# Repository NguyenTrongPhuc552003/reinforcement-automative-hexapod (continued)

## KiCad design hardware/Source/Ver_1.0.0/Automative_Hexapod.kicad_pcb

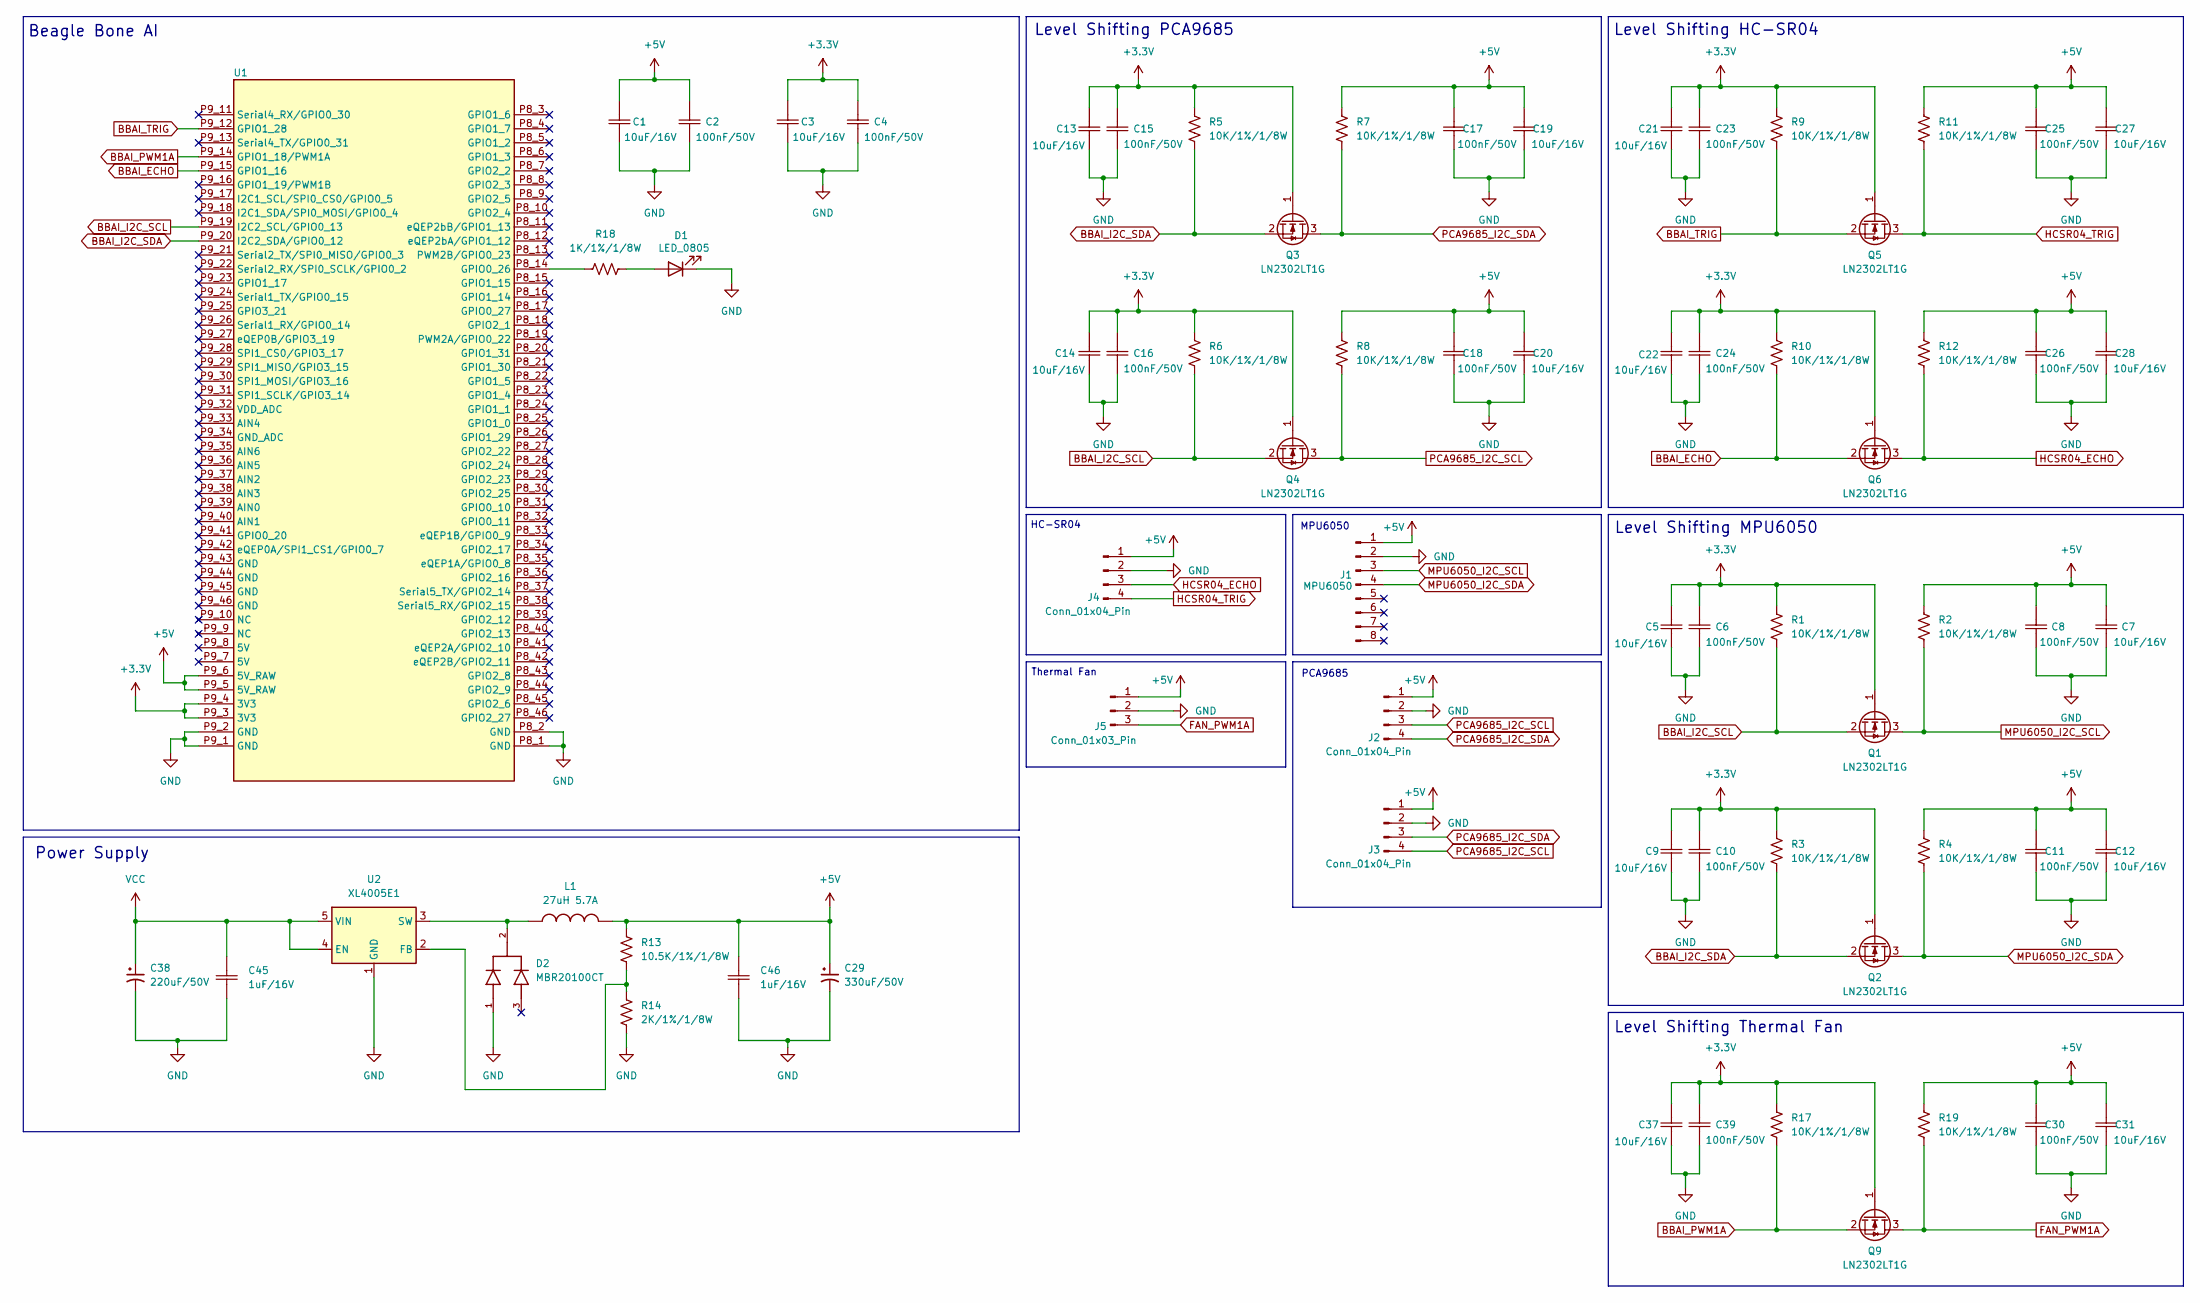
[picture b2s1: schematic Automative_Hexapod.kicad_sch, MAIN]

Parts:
C1, C3, C5, C7, C9, C12, C13, C14, C19, C20, C21, C22, C27, C28, C31, C37: 10uF/16V; Ceramic_Cap_0805
C2, C4, C6, C8, C10, C11, C15, C16, C17, C18, C23, C24, C25, C26, C30, C39: 100nF/50V; Ceramic_Cap_0805
C29: 330uF/50V; CP_Elec_10x10.5
C38: 220uF/50V; CP_Elec_10x10.5
C45, C46: 1uF/16V; Ceramic_Cap_0805
D1: LED_0805
D2: MBR20100CT; TO-220-3
J1: MPU6050
J2, J3, J4: Conn_01x04_Pin; PinHeader_1x04_P1.00mm_Vertical
J5: Conn_01x03_Pin; PinHeader_1x03_P1.00mm_Vertical
L1: 27uH 5.7A; IND_CDRH127_LDNP-470MC_SUM
Q1, Q2, Q3, Q4, Q5, Q6, Q9: LN2302LT1G; SOT23
R1, R2, R3, R4, R5, R6, R7, R8, R9, R10, R11, R12, R17, R19: 10K/1%/1/8W; Res_0805
R13: 10.5K/1%/1/8W; Res_0805
R14: 2K/1%/1/8W; Res_0805
R18: 1K/1%/1/8W; Res_0805
U1: BeagleBone_AI
U2: XL4005E1; TO-263-5

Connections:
+3.3V: C3.2, C4.2, C5.2, C6.2, C9.2, C10.2, C13.2, C14.2, C15.2, C16.2, C21.2, C22.2, C23.2, C24.2, C37.2, C39.2, Q1.1 (G), Q2.1 (G), Q3.1 (G), Q4.1 (G), Q5.1 (G), Q6.1 (G), Q9.1 (G), R1.2, R3.2, R5.2, R6.2, R9.2, R10.2, R17.2, U1.P9_3 (3V3), U1.P9_4 (3V3)
+5V: C1.2, C2.2, C7.2, C8.2, C11.2, C12.2, C17.2, C18.2, C19.2, C20.2, C25.2, C26.2, C27.2, C28.2, C29.1, C30.2, C31.2, C46.2, J1.1, J2.1, J3.1, J4.1, J5.1, L1.2, R2.2, R4.2, R7.2, R8.2, R11.2, R12.2, R13.2, R19.2, U1.P9_5 (5V_RAW), U1.P9_6 (5V_RAW)
BBAI_ECHO: Q6.2 (S), R10.1, U1.P9_15 (GPIO1_16)
BBAI_I2C_SCL: Q1.2 (S), Q4.2 (S), R1.1, R6.1, U1.P9_19 (I2C2_SCL/GPIO0_13)
BBAI_I2C_SDA: Q2.2 (S), Q3.2 (S), R3.1, R5.1, U1.P9_20 (I2C2_SDA/GPIO0_12)
BBAI_PWM1A: Q9.2 (S), R17.1, U1.P9_14 (GPIO1_18/PWM1A)
BBAI_TRIG: Q5.2 (S), R9.1, U1.P9_12 (GPIO1_28)
FAN_PWM1A: J5.3, Q9.3 (D), R19.1
GND: C1.1, C2.1, C3.1, C4.1, C5.1, C6.1, C7.1, C8.1, C9.1, C10.1, C11.1, C12.1, C13.1, C14.1, C15.1, C16.1, C17.1, C18.1, C19.1, C20.1, C21.1, C22.1, C23.1, C24.1, C25.1, C26.1, C27.1, C28.1, C29.2, C30.1, C31.1, C37.1, C38.2, C39.1, C45.1, C46.1, D1.1 (K), D2.1, J1.2, J2.2, J3.2, J4.2, J5.2, R14.1, U1.P8_1 (GND), U1.P8_2 (GND), U1.P9_1 (GND), U1.P9_2 (GND), U2.1 (GND)
HCSR04_ECHO: J4.3, Q6.3 (D), R12.1
HCSR04_TRIG: J4.4, Q5.3 (D), R11.1
MPU6050_I2C_SCL: J1.3, Q1.3 (D), R2.1
MPU6050_I2C_SDA: J1.4, Q2.3 (D), R4.1
unnamed: D1.2 (A), R18.2
unnamed: R18.1, U1.P8_14 (GPIO0_26)
unnamed: R13.1, R14.2, U2.2 (FB)
unnamed: D2.2, L1.1, U2.3 (SW)
PCA9685_I2C_SCL: J2.3, J3.4, Q4.3 (D), R8.1
PCA9685_I2C_SDA: J2.4, J3.3, Q3.3 (D), R7.1
VCC: C38.1, C45.2, U2.4 (EN), U2.5 (VIN)

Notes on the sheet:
PCA9685
HC-SR04
Thermal Fan
Level Shifting MPU6050
Beagle Bone AI
Level Shifting HC-SR04
Level Shifting Thermal Fan
MPU6050
Level Shifting PCA9685
Power Supply

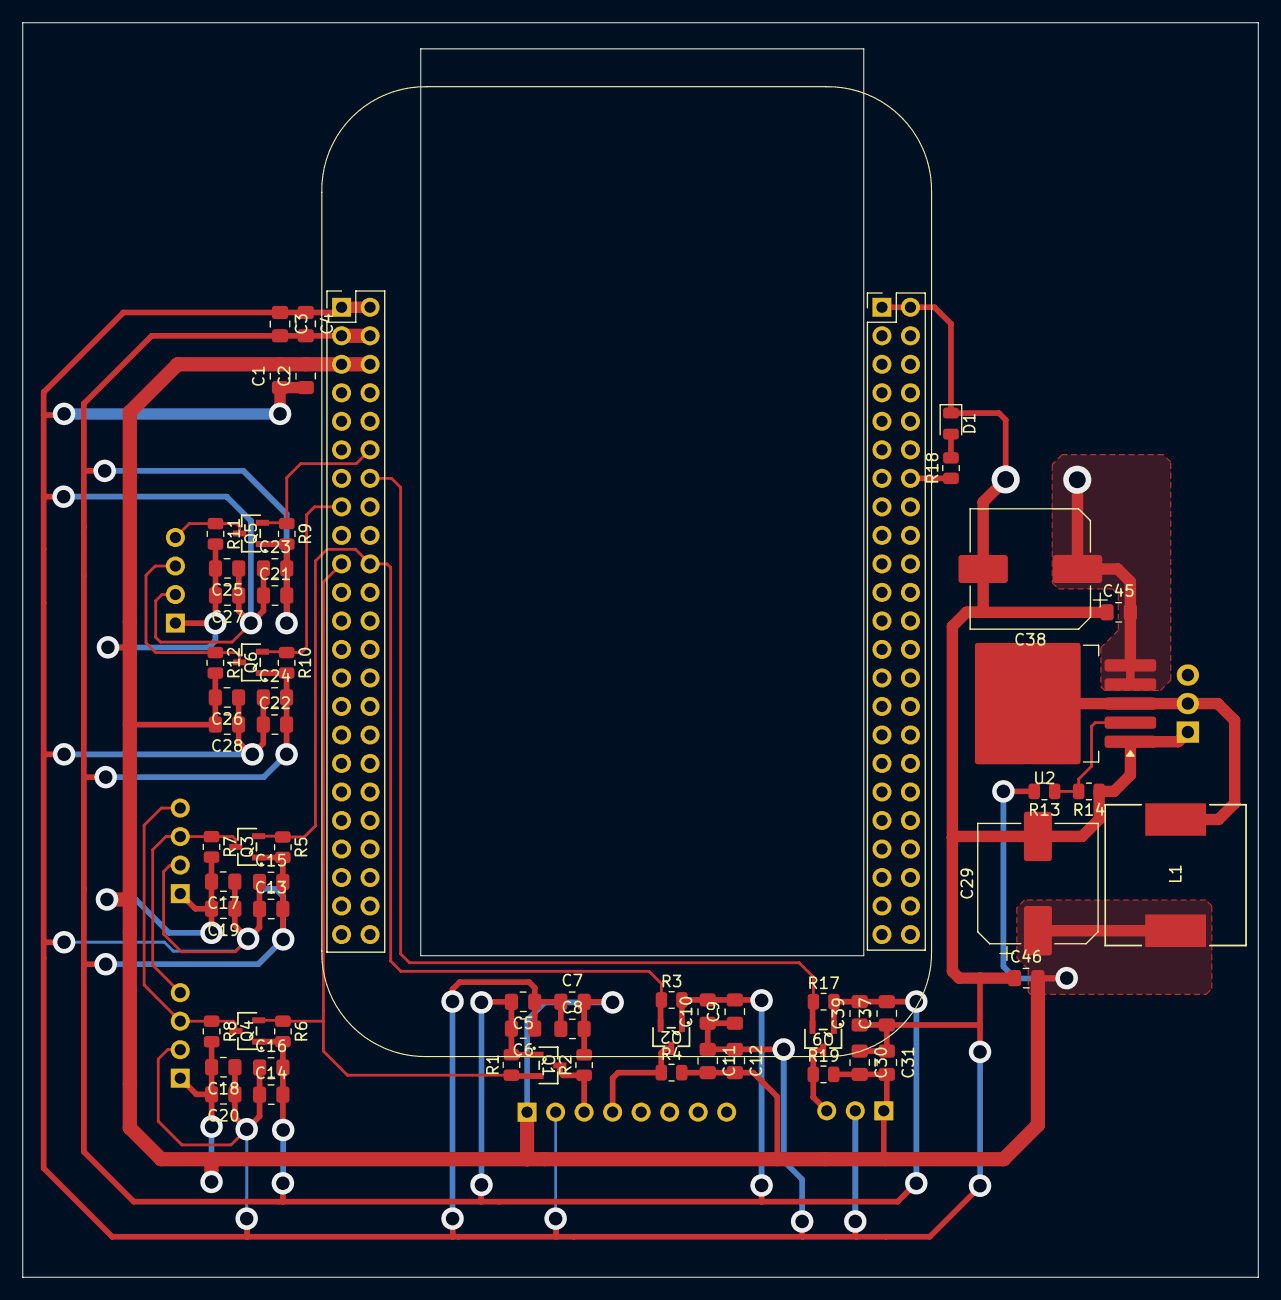
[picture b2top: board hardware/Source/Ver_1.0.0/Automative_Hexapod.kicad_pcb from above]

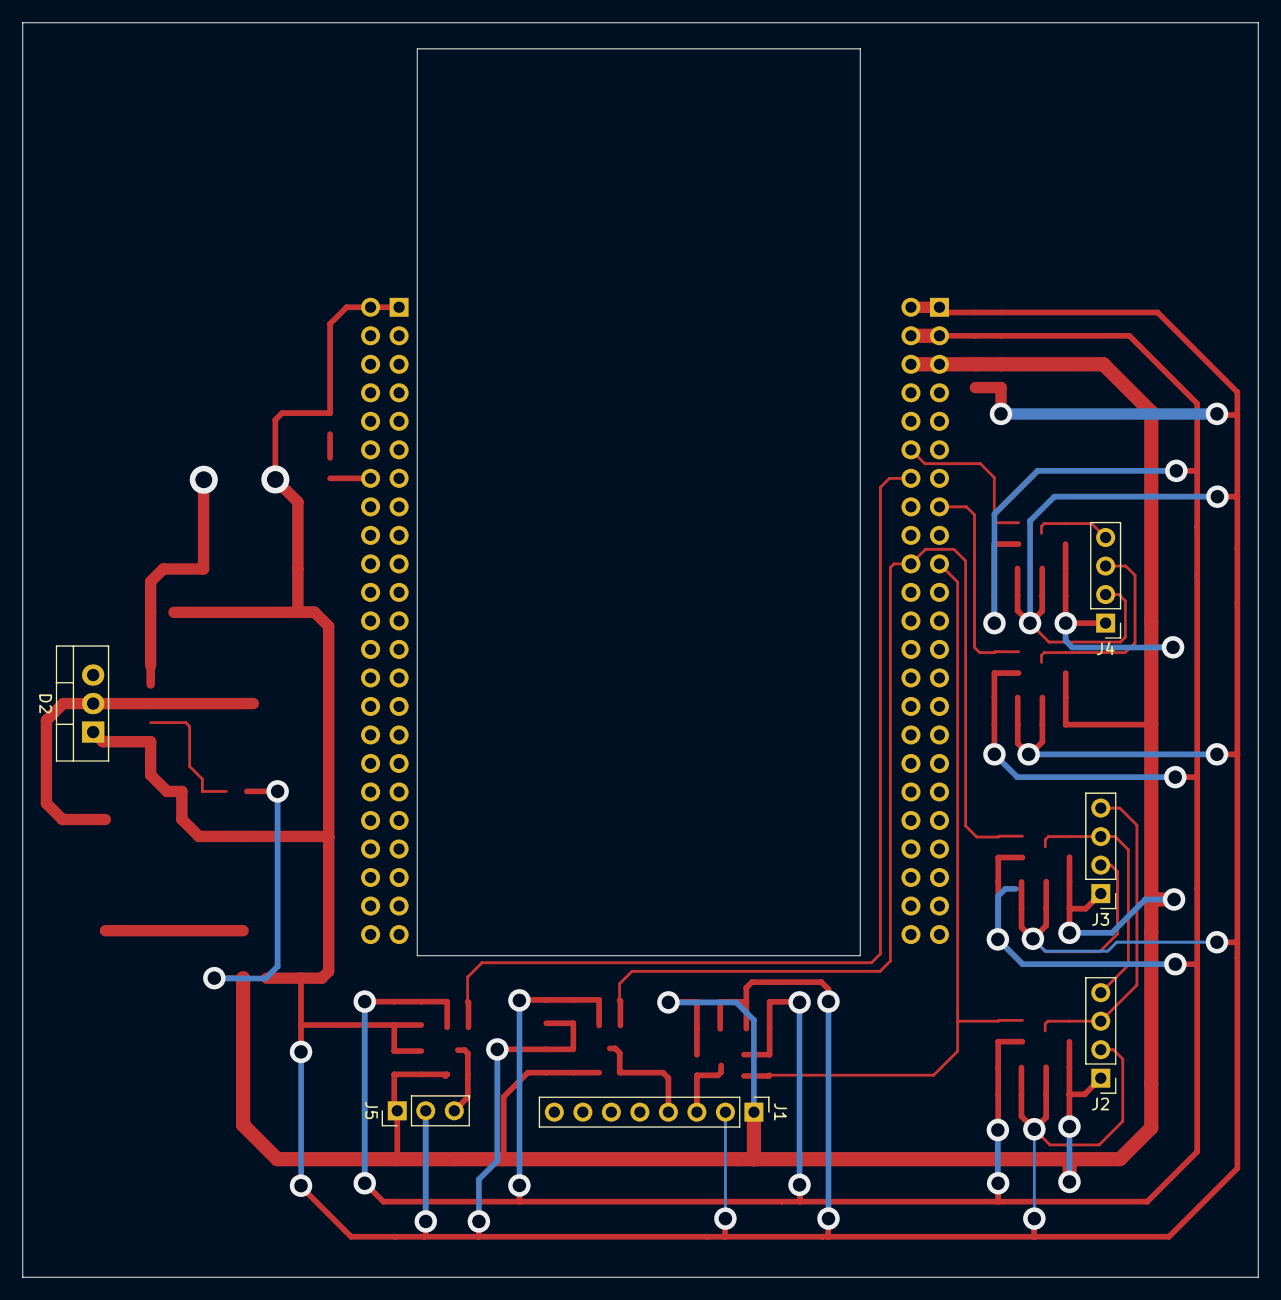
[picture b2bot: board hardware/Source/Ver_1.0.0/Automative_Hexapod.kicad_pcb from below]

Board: 2 copper layers, 110.1 x 111.8 mm, 70 parts (6 on the bottom side), 20 nets.

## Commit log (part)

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2025-02-18 Add some new features
2025-02-18 Extend and Develop some new features
2025-02-19 Add clean option for make command
2025-02-19 Modify our kernel driver for optimizations
2025-02-19 Modify our user space programs for optimizations
2025-02-20 Modify and update new features
2025-02-20 Update .gitignore and hexapod kernel driver
2025-02-22 websocket
2025-02-22 Rewrite and update user space sources
2025-02-23 Creating more static/dynamic libraries for communication between layers
2025-02-25 Intergrating the common libraries between the layers to enhance the performance
2025-02-25 Update the latest to documents
2025-02-26 Update the inverse kinematics algorithm
2025-02-26 Optimizing the general hexapod structure
2025-02-28 Update the user space patches
2025-03-05 Big updates
2025-03-06 Create an extra hexapod controller for keyboard
2025-03-10 Rewriting the user space applications from C to Cpp
2025-03-11 Upgrade the basic hexapod application features
2025-03-11 Modify the main README.md
2025-03-11 Finish the build system environment with Dockerfile
2025-03-11 Move the websocket program to the new hierachy structure
2025-03-20 Patch the kernel drivers related to the second PCA9685
2025-03-21 Modify and repair the some kernel drivers
2025-03-21 Re-structure the user space programs
2025-03-21 Rename the docker-entrypoint.sh
2025-03-24 Optimize the kernel drivers and user space programs by making them better
2025-03-27 Re-structing the user space programs's structures by making theirs more expandable and maintainable easily
2025-03-28 Patching the MPU6050 wake-up error after re-running the testing program for this peripheral
2025-03-28 Refactoring the deleted old files to new names
2025-03-29 Replace C with Cpp syntax
2025-04-03 Create an extra utils directory to make the project's structure looks better
2025-04-03 Move both install.sh and monitor.sh bash scripts to the utils directory
2025-04-03 Add both OpenCL and TIDL APIs submodule to the hexapod
2025-04-04 Add Twin Delayed DDPG algorithm implementations to improve the hexapod's movement
2025-04-11 Rename the peripherals's document names
2025-04-11 Hexapod Monitoring Application by Qt Framework
2025-04-11 Modify a little bit
2025-04-11 Modify and update the Docker environment
2025-04-11 Upgrade the build.sh script' features based on td3learn
2025-04-11 Add the build directory that contains Makefile configuration for this Qt application
2025-04-12 Update and enhance the Qt hexapod UI
2025-04-12 Fix the syntax error by replacing device to artifact
2025-04-12 Enhance the td3 algorithms based on its related API functions
2025-04-12 Remove the unnescessary libraries
2025-04-12 Rename the Qt hexapod project
2025-04-14 Ignoring the out directory
2025-04-14 Creating a building script for UML diagrams from docs/diagrams directory
2025-04-14 Adding the extra UML diagrams building with export.sh script support
2025-04-14 Adding an extra UML diagrams directory to create a system overview better
2025-04-14 Change the generated output's title without space
2025-04-14 Update the building background
2025-04-14 Update the latest documents
2025-04-15 Rename the Qt hexapod application
2025-04-15 Remove the old files
2025-04-15 Add the build configuration
2025-04-21 Modifying and fixing the td3learn algorithm
2025-04-21 Update hexapod application
2025-04-21 Update quickstart document
2025-04-21 Modify TD3Learn CMake configuration for enhancement
2025-04-26 Add SIM7600CE module
2025-04-26 Create MPU6050 and PCA9685 device tree for the better cases
2025-05-03 Fix the cleanup duplication
2025-05-03 Rename the related uml diagrams for TD3 algorithm
2025-05-03 Rename TD3 algoritm
2025-05-20 Add some comment
2025-05-20 Remove setup.sh bash script
2025-05-20 Modify and update td3learn
2025-05-20 Update Docker environment
2025-05-20 Update entrypoint.sh script to match with the current Dockerfile environment
2025-05-20 Update more features to docker-compose.yml file
2025-05-20 Change the path from static to dynamic
2025-05-20 Modify and update this script to add the QtUI building and cleaning operations
2025-05-20 Using new docker hierachy instead of the old common
2025-05-20 remove the generated file
2025-05-27 Turn this qtui into a submodule
2025-05-27 Update the diagram outputs
2025-05-27 Modify the ignored python
2025-05-27 Add a testing bash script
2025-05-27 Start to integrate the gitlab CICD process into our project
2025-05-27 Update the building script
2025-06-07 Isolate the Qt hexapod app from this repo
2025-06-07 Remove tracked PNG files from docs/diagrams/out/
2025-06-07 Ignore the generated .png files from diagram directory
2025-06-07 Keep diagram PNG files tracked in Git
2025-06-07 Create a directory to stored the generated files after building the UML programs
2025-06-07 Add the HC-SR04 sensor's documents
2025-06-08 Change the app features
2025-06-14 Modify and add more changes to support a new integrated sensor
2025-06-15 Add the BeagleBone AI schematic
2025-06-15 Update the ultrasonic API functions's implementations using sysfs interface instead of libgpiod usage
2025-06-15 Update the ultrasonic testing program using new its API functions
2025-06-15 Move the beagleone AI images to its compatible directory from resource
2025-06-20 Isolate the building Docker environment from build.Dockerfile to multiple environments
2025-06-23 Modify and delete the common Docker configuration environment, isolate them into multiple environments instead
2025-06-23 Add the BeagleBone Linux kernel repository
2025-06-25 Replace the HC-SR04 sensor with new one using the ADC mechanism
2025-06-25 Replace the HC-SR04 sensor documents with new one
2025-06-25 Remove the kernel building Docker environment
2025-06-26 Change the buiding options with new one shoter and more clearly
2025-06-28 Schematic V1.0.0
2025-06-28 upload pcb
2025-06-28 Adding the logger implementation
2025-06-28 Change the leg's servo order
2025-06-29 update folder hardware
2025-06-29 upload test ir distance
2025-06-29 Update Reference Project for IR Sensor
2025-07-01 Update Library for Ver 2
2025-07-04 Create and implement the pair of ultrasonic and its testing program
2025-07-06 update pcb and schematic
2025-07-06 update pcb
2025-07-06 Adding new packaging mechanism to combine all builtin files into a package
2025-07-06 Add one more adxl345 object to the for loop
2025-07-06 Remove the hexapod files from both inc and src directories, using the main entry instead
2025-07-06 Add the adxl345 document
2025-07-06 Add the thesis submodule
2025-07-06 Extend the IMU sensor by adding new one, ADXL345
2025-07-06 Extend the related files to support the switch mechanism between mpu6050 and adxl345 devices
2025-07-06 Modify the device ID to match with the i2c address
2025-07-06 Reformating this app directory's files
2025-07-06 Update the image diagram outputs
2025-07-06 Add the ultrasonic documents for HC-SR04 sensor model
2025-07-06 Rename the hexapod_controller to hexapod_app
2025-07-06 Replace the mpu6050_cleanup() function's position to the other one
2025-07-06 Remove the TI kernel linux, it will be moved to the other branch in the future
2025-07-07 Update the ignored and submodule parts for .git files
2025-07-07 Update the thesis path
2025-07-08 Add a MIT license
2025-07-08 Create a cleanup function for ultility option
2025-07-08 Mark the use license with the source file at the beginning of each file
2025-07-08 Update the .puml files to the latest
2025-07-08 Replace the old building options to scripts/build.sh
2025-07-08 Update the thesis branch to the main instead of the other
2025-07-08 Get updates from the thesis's main branch
2025-07-08 Ignore the thesis templates
2025-07-08 Supplement the .ignore extension to ignore all thesis templates
2025-07-08 Change the line that contains hcmus_logo to mainHCMUS
2025-07-08 Get the latest updates after rebuilding all .puml files
2025-07-08 Mark these directories as unused components until being removed
2025-07-09 Modify and update deployment.puml
2025-07-09 Update all .puml files
2025-07-09 Update all .png files from the .puml building
2025-07-09 Update thesis
2025-07-09 Add more .drawio files inside this diagrams directory
2025-07-09 Revise the block comment in the header of main.py
2025-07-09 Modify and update .tex files
2025-07-11 Remove the MSSV field at the end of this file
2025-07-11 Update the file content
2025-07-12 Udpate .gitignore file to supplement the generated bin directory
2025-07-12 Rename the kernel driver dependencies from .ko to .o extension files
2025-07-12 Modify and enhance the thesis contents
2025-07-13 Generate Gerber V1.1.0
2025-07-14 Rename and relocate to the contents directory
2025-07-14 Supplement the WSL2 environmen, this will be splitted to the other branch in the future
2025-07-15 Modify and create new category directory
2025-07-15 Refine notes.txt
2025-07-16 Remove redundant sections
2025-07-16 Update thesis based on its latest commit
2025-07-16 Fork the submodules to my github repos
2025-07-18 Porting the driver building environment from Butser to Bullseye, also to its toolchains version (8 -> 10)
2025-07-18 Fixing the stricter attribute checks in newer GCC toolchains
2025-07-18 Remove the unneccessary dependencies
2025-07-18 Supplement the BeagleBone MAC address variable
2025-07-18 Export BOM for ver 1.1.0
2025-07-20 Rename some directories and create new ones
2025-07-20 Update .png files
2025-07-20 Move the .puml files compiler to the other place
2025-07-21 Commit the thesis status based on its latest commit
2025-07-22 Start to integrate new algorithm - CPG by replacing and removing the unnecessary old API libraries
2025-07-22 Add new testing program
2025-07-22 Supplement the CPG algorithm building
2025-07-22 Modify and update to replace the old API (IK + Gait) with new one
2025-07-22 Ignore the ABI combatibility
2025-07-23 Remove the excess methods from file configuration part
2025-07-23 Update all PlantUML files by replacing the old algorithm with CPG one
2025-07-23 Create a update summary for latest diagrams
2025-07-23 Rename branch from main to CPG
2025-07-23 Rename branch from main to GaitIK
2025-07-23 Reformat these bash scripts better
2025-07-24 Porting device drivers and theirs building environment from 4.14.108 to 5.10.168
2025-07-24 Remove all related ADXL345 sensor parts
2025-07-24 Restructure and append new supported board
2025-07-24 Replace BeagleBone AI with the other branch - Black
2025-07-24 Update .puml file to match to the current target board
2025-07-24 Update .png file based on its directory's latest commit
2025-07-24 Release the final output temporarily
2025-07-25 Remove all legacy algorithms (Gait + IK) from the current new one - CPG
2025-07-25 Change the control operation from manual to autonomous
2025-07-25 Create a .service systemd file to start our hexapod automatically at startup
2025-07-25 Modify both preinst and prerm to add and remove our .service systemd file
2025-07-25 Modify the create_package_structure function to append the .serivce systemd file creation
2025-07-25 Restructure all .tex file to match with CPG algorithm better
2025-07-25 Modify these .tex files better
2025-07-25 Add a .service systemd file
2025-07-25 Clean this up
2025-07-26 Remove all hexapod_driver kernel object installations
2025-07-26 Update all configuration files
2025-07-26 Update all source codes
2025-07-26 Correct the GPIO mapping
2025-07-27 Update new feature to enhance the hexapod movements
2025-07-27 Update new features
2025-07-27 Update the physical hexapod parameters more suitable
2025-07-27 Generate PDF Schematic Ver1.1.0 and add README.md
2025-07-27 Supplement more documents
2025-07-27 Update the alternative board and sensors
2025-07-27 Update the HC-SR04 ultrasonic sensor to correct the pair of this sensor's pins (TRIG & ECHO)
2025-07-27 Branch to origin/Thesis
2025-07-27 Update all files
2025-07-27 Rebuild all .tex files to generate new main.pdf
2025-07-28 Update hexapod source
2025-07-28 Supplement the assembling process image
2025-07-28 Update all .tex files
2025-07-28 Update the controlling flow images
2025-07-28 Update the driver architecture image
2025-07-29 Remove the HC-SR04 device driver
2025-07-29 Modify the abstraction
